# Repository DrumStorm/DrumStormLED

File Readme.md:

# Drumstorm LED

This project contains the Software and Hardware for the LED Controllers of Drumstorm.

## Hardware
Das [KiCAD](https://www.kicad.org/)-Projekt für die Hardware befindet sich im Hardware Ordner.

## Software
Das [Arduino](https://www.arduino.cc/)-Projekt für die Software befindet sich im Software Ordner.

### Programmierung
Für die Programmierung der Attiny85

kann ein Arduino Board (z.B. Arduino Uno, Arduino Mega) verwendet werden.
Eine Anleitung dafür, wie man dies macht ist unter https://www.instructables.com/Program-an-ATtiny-with-Arduino/ zu finden.

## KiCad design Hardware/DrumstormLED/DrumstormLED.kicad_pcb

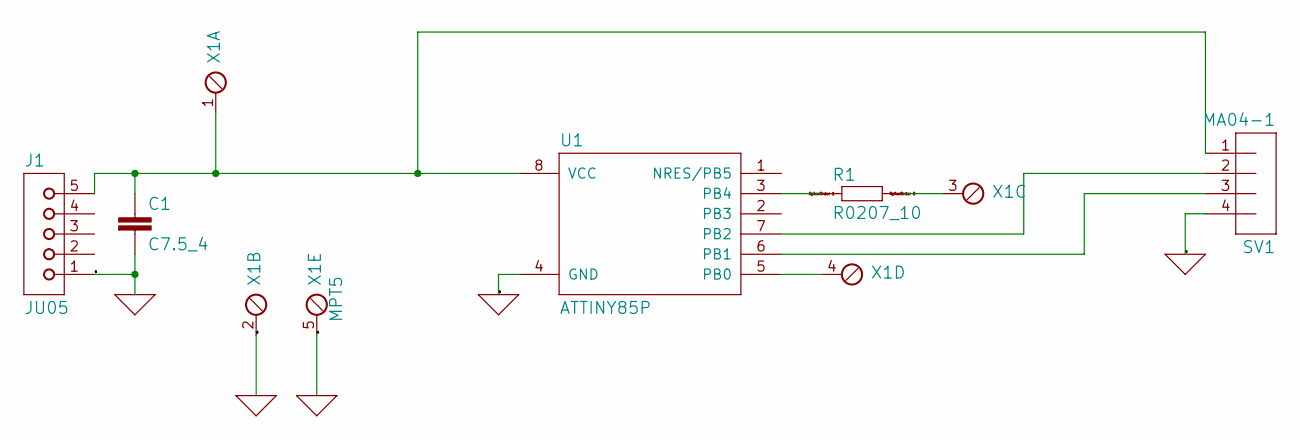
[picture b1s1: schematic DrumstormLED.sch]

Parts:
C1: C7.5_4; C7.5B4
J1: JU05
R1: R0207_10; 0207_10
SV1: MA04-1
U1: ATTINY85P; PDIP08_300MIL
X1: MPT5; 5POL254

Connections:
0: C1.2, J1.1, SV1.4, U1.4 (GND), X1.2, X1.5
unnamed: C1.1, J1.5, SV1.1, U1.8 (VCC), X1.1
unnamed: R1.1, U1.3 (PB4)
unnamed: R1.2, X1.3
unnamed: SV1.2, U1.7 (PB2)
unnamed: SV1.3, U1.6 (PB1)
unnamed: U1.5 (PB0), X1.4

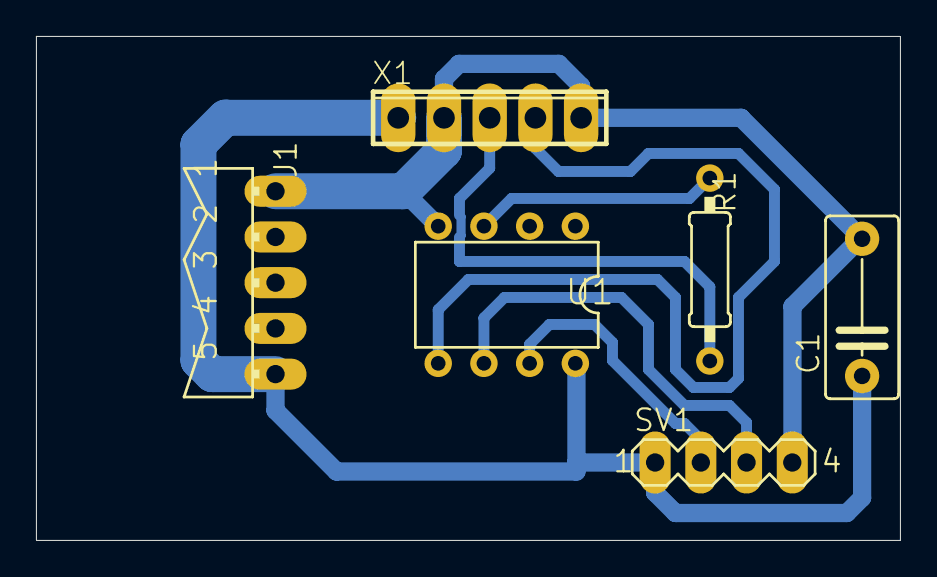
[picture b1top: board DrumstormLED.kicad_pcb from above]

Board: 2 copper layers, 48.0 x 28.0 mm, 6 parts (0 on the bottom side), 7 nets.

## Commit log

2020-10-26 inital commit
2021-03-22 removed confusing and unneccesary files
2021-09-22 cleaned up project
2021-09-22 added documentationadded documentation.
2021-09-22 removed visual studio data
